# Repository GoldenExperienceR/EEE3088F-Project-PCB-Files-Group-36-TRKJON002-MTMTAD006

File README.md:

# EEE3088F-Project-PCB-Files-Group-36-TRKJON002-MTMTAD006

EEE3088F Project Power PCB KiCad Design

## Project Overview

This repository contains the design files for the power PCB subsystem of a micro mouse robot, a project undertaken as part of the EEE3088F course. The power PCB is a crucial component responsible for providing and managing power for the entire micro mouse system, enabling its autonomous navigation capabilities.

## Project Requirements

The power PCB design is required to meet the following specifications:

* Operate up to 4 motors bidirectionally. These include 2x brushed DC motors which could each draw 200mA at the highest voltage of a 1S1P battery. The other 2x motors are for the auxiliary connection and need to operate 500mA each.
* Place an INA219 for monitoring the battery on the I2C Bus and configure it correctly with respect to the hardware (cannot have BOTH A0 AND A1 on GND).
* Charge the battery from the 9V input pin.
* Have two charging modes for a higher and lower charging current for the battery (200mA ±100mA, and approximately 600mA±100mA from the battery perspective).
* Integrate USB C and get 9V out of the USB Host.
* Provide 2x External Load Switching at 1A each (High Side connected to your 5V).
* Provide a 3v3 5% accuracy (300mA max) and 5V Out 5% accuracy (1.5A max).
* Provide an ON/OFF switch. **OFF state:** battery draw <30uA. **ON state:** can provide your robot peak current of 2A. The switch needs to shut down 5V and 3V3.

## Repository Structure

This repository utilizes the following branches to manage the project's development:

* **main:** This branch contains the first iteration of the PCB design.
* **jonathans\_branch:** This branch includes separate modifications that were developed and subsequently merged into the `main` branch.
* **design2:** This branch represents the culmination of all changes made throughout the project and contains the final design of the power PCB. For the latest and final version of the design, please refer to this branch.

## Cloning Instructions
To obtain the latest version of the power PCB design, you can clone the `design2` branch directly using the following command:

```bash
git clone -b design2 [https://github.com/GoldenExperienceR/EEE3088F-Project-PCB-Files-Group-36-TRKJON002-MTMTAD006.git](https://github.com/GoldenExperienceR/EEE3088F-Project-PCB-Files-Group-36-TRKJON002-MTMTAD006.git)

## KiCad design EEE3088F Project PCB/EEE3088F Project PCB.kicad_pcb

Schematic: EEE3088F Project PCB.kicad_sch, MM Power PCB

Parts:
C1, C6: 0.01uF; C_0805_2012Metric_Pad1.18x1.45mm_HandSolder
C2, C4: 2.2uF; C_0603_1608Metric_Pad1.08x0.95mm_HandSolder
C3, C5, C21: 10uF; C_0805_2012Metric_Pad1.18x1.45mm_HandSolder
C7: 10uF; C_0402_1005Metric_Pad0.74x0.62mm_HandSolder
C8, C11, C12, C13, C14, C15, C17: 1uF; CAPC3216X180N
C16, C18: 0.1uF; C_0402_1005Metric_Pad0.74x0.62mm_HandSolder
C19: 0.33u; C_0805_2012Metric_Pad1.18x1.45mm_HandSolder
C20: 0.1u; C_0402_1005Metric_Pad0.74x0.62mm_HandSolder
D1: MBR230LS; D_SOD-123F
H1: MountingHole; MountingHole_2.2mm_M2_DIN965_Pad
J1: JST PH 2.00mm connector; JST_PH_S2B-PH-K_1x02_P2.00mm_Horizontal
J2: HRO_TYPE-C-31-M-12
JP1: V_BATT_CHRG Bridge; SolderJumper-2_P1.3mm_Bridged2Bar_Pad1.0x1.5mm
JP2: R_PROG_1 Bridge; SolderJumper-3_P1.3mm_Bridged2Bar12_RoundedPad1.0x1.5mm_Num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
JP3: R_PROG_2 Bridge; SolderJumper-3_P1.3mm_Bridged2Bar12_RoundedPad1.0x1.5mm_Num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
JP4, JP5, JP6, JP7, JP8, JP9, JP10: SolderJumper_2_Open; SolderJumper-2_P1.3mm_Open_RoundedPad1.0x1.5mm
JP11: SolderJumper_2_Bridged; SolderJumper-2_P1.3mm_Bridged2Bar_RoundedPad1.0x1.5mm
L1: 22uH; L_Coilcraft_1515SQ-47N
Q1: NPN; SOT-23_Handsoldering
R1, R2: 3.3k; R_0603_1608Metric
R3: 1k; RESC3115X65N
R4: 10k; RESC3115X65N
R5: 470; R_0805_2012Metric_Pad1.20x1.40mm_HandSolder
R6, R11, R12, R14: 160m; R_2512_6332Metric_Pad1.40x3.35mm_HandSolder
R7: 300; R_0805_2012Metric_Pad1.20x1.40mm_HandSolder
R8: 2200; R_0603_1608Metric_Pad0.98x0.95mm_HandSolder
R9, R10: 10; R_1206_3216Metric_Pad1.30x1.75mm_HandSolder
R13: 100; R_0805_2012Metric_Pad1.20x1.40mm_HandSolder
R_PROG_1: 2k; R_0402_1005Metric_Pad0.72x0.64mm_HandSolder
R_PROG_2: 6.2k; R_0603_1608Metric
S1: 74LVC2G66DP; Manufacturer_Part_Number 74LVC2G66DP; Mouser Part Number N/A
SW1: SS-12D10L3; SS-12D10G5_XKB
TP1: HV Test Point; TestPoint_Pad_1.0x1.0mm
TP3, TP7, TP9: TestPoint; TestPoint_Pad_2.0x2.0mm
TP4, TP6, TP8, TP10, TP11, TP12, TP13, TP18, TP19, TP20, TP21: TestPoint; TestPoint_Pad_1.0x1.0mm
U1: DRV8833PWR; TSSOP-16-1EP_4.4x5mm_P0.65mm_EP3x3mm
U2: DRV8833PWPR; TSSOP-16-1EP_4.4x5mm_P0.65mm_EP3x3mm
U3: INA219AxD; TSOT-23-8
U4: CH224K; SSOP-10-1EP_3.9x4.9mm_P1mm_EP2.1x3.3mm
U6: MIC5504-1.2YM5; SOT-23-5
U7: SX1308; SOT-23-6
U8, U9: TPS22965DSGR; DFN-8-1EP_2x2mm_P0.5mm_EP0.9x1.6mm; DigiKey_Part_Number 296-39362-2-ND
U10: LM7805L-TF3-T; TO-220F-3_Vertical
U11: TC4056A.; SOIC127P600X175-9N
am1: 2x16 (2.54mm pin pitch) pin header; PinHeader_2x16_P2.54mm_Vertical

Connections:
/2E: JP11.2 (B), R13.2, S1.3 (2E), TP6.1
/3V3 Out: C12.1, S1.8 (VCC), TP7.1, U6.5 (VOUT), am1.18
/5V Out: C13.1, C15.2, C17.2, D1.1 (K), R8.1, R13.1, TP9.1, U8.1 (VIN), U8.2 (VIN), U8.4 (VBIAS), U9.1 (VIN), U9.2 (VIN), U9.4 (VBIAS), am1.20
/Battery: J1.1, JP4.1 (A), JP7.2 (B), JP8.1 (A), R6.2, SW1.3, TP8.1, U3.2 (A0), am1.14
/CC1: J2.A5 (CC1), U4.7 (CC1)
/CC2: J2.B5 (CC2), U4.6 (CC2)
/CTRL_EXT_LOAD1: U8.3 (ON), am1.25
/CTRL_EXT_LOAD2: U9.3 (ON), am1.7
/DN: J2.A7 (DN), J2.B7 (DN), U4.5 (DM)
/DP: J2.A6 (DP), J2.B6 (DP), U4.4 (DP)
/EXT_LOAD1_OUT: C16.2, JP9.2 (B), R9.1, U8.7 (VOUT), U8.8 (VOUT), am1.21
/EXT_LOAD2_OUT: C18.2, JP10.2 (B), R10.1, U9.7 (VOUT), U9.8 (VOUT), am1.11
/FAST_CHARGE_CTRL: R5.1, S1.7 (1E), TP4.1, am1.13
/HV: C19.1, TP1.1, U4.10 (PG), U10.1 (VI), am1.22
/I2C1_SCL: R2.1, am1.16
/I2C1_SDA: R1.2, am1.17
/MOTOR1_A_OUT: U1.2 (AOUT1), am1.32
/MOTOR1_B_OUT: U1.4 (AOUT2), am1.31
/MOTOR1_CTRL1: TP10.1, U1.16 (AIN1), am1.28
/MOTOR1_CTRL2: TP11.1, U1.15 (AIN2), am1.30
/MOTOR2_CTRL1: TP12.1, U1.9 (BIN1), am1.4
/MOTOR2_CTRL2: TP13.1, U1.10 (BIN2), am1.6
/MOTOR3_A_OUT: JP5.1 (A), R12.2, am1.27
/MOTOR3_B_OUT: U2.4 (AOUT2), am1.29
/MOTOR3_CTRL1: TP18.1, U2.16 (AIN1), am1.24
/MOTOR3_CTRL2: TP19.1, U2.15 (AIN2), am1.26
/MOTOR4_CTRL1: TP20.1, U2.9 (BIN1), am1.8
/MOTOR4_CTRL2: TP21.1, U2.10 (BIN2), am1.10
/Motor2_A_OUT: U1.7 (BOUT1), am1.2
/Motor2_B_OUT: U1.5 (BOUT2), am1.1
/Motor4_A_OUT: JP6.1 (A), R14.1, am1.3
/Motor4_B_OUT: U2.5 (BOUT2), am1.5
/PROG: R_PROG_1.2, R_PROG_2.1, U11.2 (PROG)
/USART2_RX: am1.9
/USART2_TX: am1.12
/VBUS: J2.A4_B9 (VBUS), J2.B4_A9 (VBUS), R3.1, R4.1
/VDD: C8.1, R3.2, U4.1 (VDD)
/V_BATT_CHRG: C20.1, JP1.1 (A), U10.3 (VO)
/V_sensing: C1.1, C3.2, C5.2, C6.1, C11.1, C14.1, JP7.1 (A), L1.1, R11.1, U1.12 (VM), U2.12 (VM), U3.7 (IN-), U6.1 (VIN), U7.5 (IN)
/V_switch: C7.1, JP8.2 (B), R11.2, SW1.2, U3.5 (VS), U3.8 (IN+), U6.3 (EN), U7.4 (EN)
GND: C2.1, C3.1, C4.1, C5.1, C7.2, C8.2, C11.2, C12.2, C13.2, C14.2, C15.1, C16.1, C17.1, C18.1, C19.2, C20.2, C21.1, J1.2, J2.A1_B12 (GND), J2.B1_A12 (GND), J2.S1 (shield), JP2.3 (B), JP3.3 (B), JP9.1 (A), JP10.1 (A), Q1.3 (E), R7.2, R9.2, R10.2, S1.1 (1Y), S1.4 (GND), S1.5 (2Y), SW1.1, TP3.1, U1.3 (AISEN), U1.6 (BISEN), U1.13 (GND), U1.17 (GND), U2.3 (AISEN), U2.6 (BISEN), U2.13 (GND), U2.17 (GND), U3.1 (A1), U3.6 (GND), U4.2 (CFG2), U4.3 (CFG3), U4.9 (CFG1), U4.11 (GND), U6.2 (GND), U7.2 (GND), U8.5 (GND), U8.6 (CT), U8.9 (GND), U8.9_1 (GND), U8.9_2 (GND), U9.5 (GND), U9.6 (CT), U9.9 (GND), U9.9_1 (GND), U9.9_2 (GND), U10.2 (GND), U11.3 (GND), am1.19, am1.23; also elsewhere on the board
unnamed: D1.2 (A), L1.2, U7.1 (SW)
unnamed: JP1.2 (B), U11.4 (VCC)
unnamed: JP2.1 (A), R_PROG_1.1
unnamed: JP2.2 (C), S1.2 (1Z)
unnamed: JP3.1 (A), S1.6 (2Z)
unnamed: JP3.2 (C), R_PROG_2.2
unnamed: C21.2, JP4.2 (B), R6.1, U11.5 (BAT)
unnamed: JP5.2 (B), R12.1, U2.2 (AOUT1)
unnamed: JP6.2 (B), R14.2, U2.7 (BOUT1)
unnamed 50: JP11.1 (A), Q1.1 (C); also elsewhere on the board
unnamed 51: Q1.2 (B), R5.2; also elsewhere on the board
unnamed: C1.2, U1.11 (VCP)
unnamed: C2.2, U1.14 (VINT)
unnamed: C6.2, U2.11 (VCP)
unnamed: C4.2, U2.14 (VINT)
unnamed: R2.2, U3.4 (SCL)
unnamed: R1.1, U3.3 (SDA)
unnamed: R4.2, U4.8 (VBUS)
unnamed: R7.1, R8.2, U7.3 (FB)

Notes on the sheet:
PIN CONNECTORS AND BATTERY CONNECTOR
INA219 BATTERY CURRENT SENSOR
USB INTEGRATION
Fast and Slow Charging Modes
MOTOR DRIVER
x2 Load switching at 1 A
ON/OFF switch
3V3 300mA voltage regulator
5v 1.5A voltage regulator

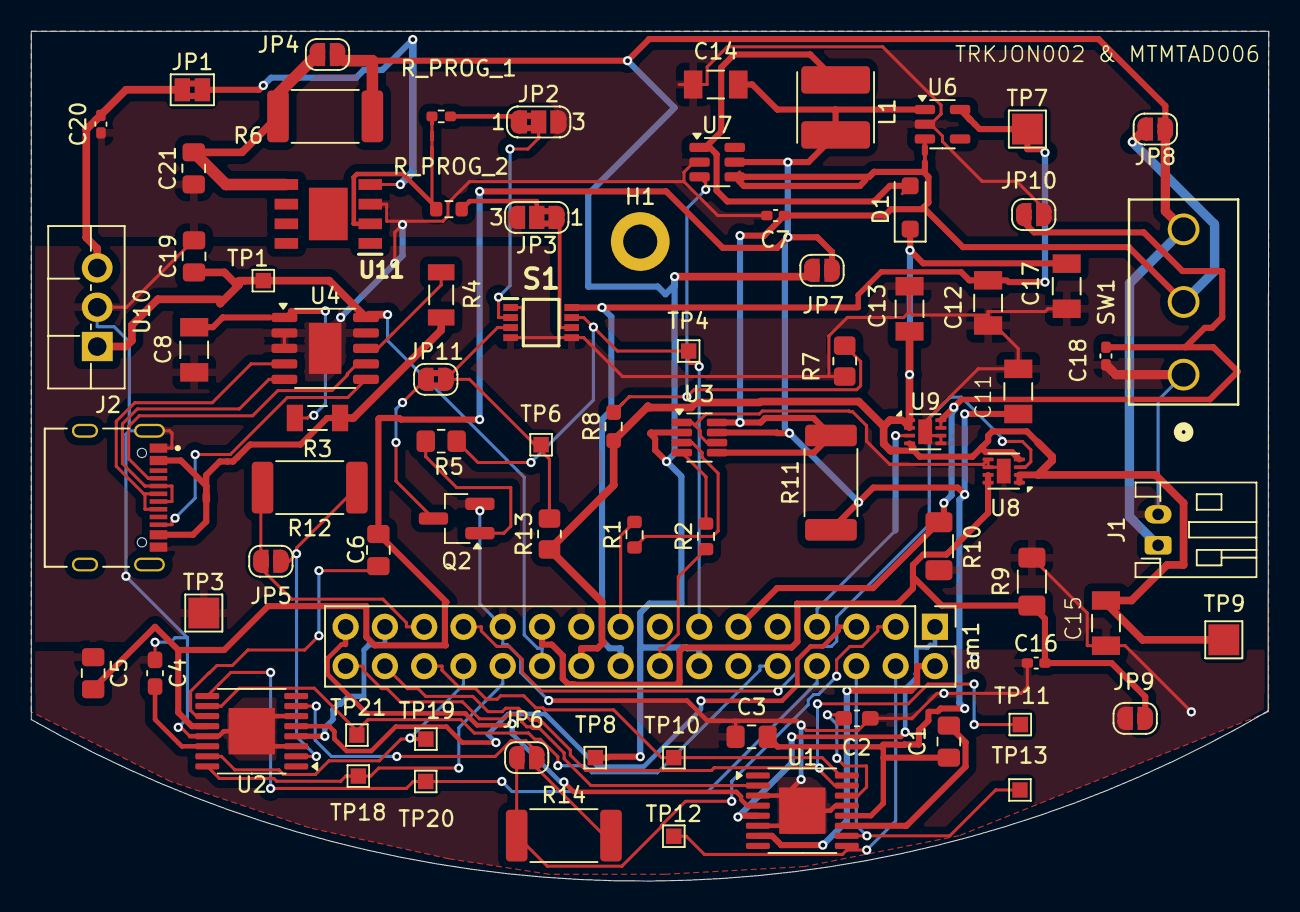
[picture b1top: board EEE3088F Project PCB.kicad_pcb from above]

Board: 2 copper layers, 80.0 x 54.9 mm, 80 parts (0 on the bottom side), 58 nets.

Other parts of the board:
Q2: NPN; SOT-23_Handsoldering

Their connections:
GND: Q2.2 (E); also elsewhere on the board
unnamed 50: Q2.3 (C); also elsewhere on the board
unnamed 51: Q2.1 (B); also elsewhere on the board

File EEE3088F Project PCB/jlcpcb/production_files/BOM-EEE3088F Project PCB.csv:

Comment,Designator,Footprint,LCSC,Quantity
TPS22965DSGR,"U8,U9",DFN-8-1EP_2x2mm_P0.5mm_EP0.9x1.6mm,C122837,2
0.1uF,"C16,C18,C20",C_0402_1005Metric_Pad0.74x0.62mm_HandSolder,C1525,3
10uF,C7,C_0402_1005Metric_Pad0.74x0.62mm_HandSolder,C15525,1
10uF,"C21,C3,C5",C_0805_2012Metric_Pad1.18x1.45mm_HandSolder,C15850,3
~,J2,HRO_TYPE-C-31-M-12,C165948,1
0.01uF,"C1,C6",C_0805_2012Metric_Pad1.18x1.45mm_HandSolder,C1710,2
300,R7,R_0805_2012Metric_Pad1.20x1.40mm_HandSolder,C17617,1
100,"R13,R5",R_0805_2012Metric_Pad1.20x1.40mm_HandSolder,C17710,2
10k,R4,RESC3115X65N,C17902,1
10,"R10,R9",R_1206_3216Metric_Pad1.30x1.75mm_HandSolder,C17903,2
1uF,"C11,C12,C13,C14,C15,C17,C8",CAPC3216X180N,C1848,7
NPN,Q2,SOT-23_Handsoldering,C2145,1
3.3k,"R1,R2",R_0603_1608Metric,C22978,2
2.2uF,"C2,C4",C_0603_1608Metric_Pad1.08x0.95mm_HandSolder,C23630,2
74LVC2G66DP,S1,74LVC2G66DP,C282354,1
22uH,L1,L_Coilcraft_1515SQ-47N,C2929420,1
SS-12D10L3,SW1,SS-12D10G5_XKB,C319013,1
0.33u,C19,C_0805_2012Metric_Pad1.18x1.45mm_HandSolder,C342635,1
MBR230LS,D1,D_SOD-123F,C391533,1
2k,R_PROG_1,R_0402_1005Metric_Pad0.72x0.64mm_HandSolder,C4109,1
2200,R8,R_0603_1608Metric_Pad0.98x0.95mm_HandSolder,C4190,1
6.2k,R_PROG_2,R_0603_1608Metric,C4260,1
1k,R3,RESC3115X65N,C4410,1
DRV8833PWR,"U1,U2",TSSOP-16-1EP_4.4x5mm_P0.65mm_EP3x3mm,C50506,2
160m,"R11,R12,R14,R6",R_2512_6332Metric_Pad1.40x3.35mm_HandSolder,C5375485,4
LM7805L-TF3-T,U10,TO-220F-3_Vertical,C71107,1
TC4056A.,U11,SOIC127P600X175-9N,C7588528,1
SX1308,U7,SOT-23-6,C78162,1
INA219AxD,U3,TSOT-23-8,C87469,1
MIC5504-1.2YM5,U6,SOT-23-5,C88419,1
CH224K,U4,SSOP-10-1EP_3.9x4.9mm_P1mm_EP2.1x3.3mm,C970725,1
JST PH 2.00mm connector,J1,JST_PH_S2B-PH-K_1x02_P2.00mm_Horizontal,,1
2x16 (2.54mm pin pitch) pin header,am1,PinHeader_2x16_P2.54mm_Vertical,,1
HV Test Point,TP1,TestPoint_Pad_1.0x1.0mm,,1
TestPoint,TP4,TestPoint_Pad_1.0x1.0mm,,1
TestPoint,TP6,TestPoint_Pad_1.0x1.0mm,,1
TestPoint,TP3,TestPoint_Pad_2.0x2.0mm,,1
TestPoint,TP7,TestPoint_Pad_2.0x2.0mm,,1
TestPoint,TP9,TestPoint_Pad_2.0x2.0mm,,1
TestPoint,TP19,TestPoint_Pad_1.0x1.0mm,,1
TestPoint,TP10,TestPoint_Pad_1.0x1.0mm,,1
TestPoint,TP21,TestPoint_Pad_1.0x1.0mm,,1
TestPoint,TP20,TestPoint_Pad_1.0x1.0mm,,1
TestPoint,TP18,TestPoint_Pad_1.0x1.0mm,,1
TestPoint,TP13,TestPoint_Pad_1.0x1.0mm,,1
TestPoint,TP12,TestPoint_Pad_1.0x1.0mm,,1
TestPoint,TP11,TestPoint_Pad_1.0x1.0mm,,1
TestPoint,TP8,TestPoint_Pad_1.0x1.0mm,,1

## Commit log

2025-03-21 intial commit
2025-03-22 added resistor in parallel
2025-03-22 commiting local changes 22/03/2025
2025-03-22 resistor in series with a LED
2025-03-22 resistor in parallel
2025-03-23 2x16 pin connector & JST PH 2.00 connector
2025-03-25 added pin net labels to connectors
2025-03-25 added a calaculations section, and my motor driver circuit
2025-03-25 adjusted layout slightly
2025-03-26 completed power module
2025-03-26 3/26/2025 - 8:00pm
2025-03-26 Resolved merge conflicts and merged jonathans_branch into main
2025-03-26 Added Current sensor INA219
2025-03-26 Added current sensor
2025-03-27 adjustments
2025-03-27 corrected sensor design and relabelled Vcc label to Battery
2025-03-27 added footprints to all motor driver components
2025-03-28 added usb c integration with footprints
2025-03-28 added regulatores, updated outputs, added on/off switch
2025-03-28 adjusted shunt resistance
2025-03-28 finished circuit
2025-04-01 Added student numbers, corrected board boundries, placed connectors (USB, JST, & pin headers)
2025-04-05 added fault managment and testing points for USB Integration and Charging requirments
2025-04-05 ajusted some testing points and added footprints for USB integration + half of the charging requirments
2025-04-07 added footprints to all my componets, placed all components on the board, and added all my jlcpcb part numbers
2025-04-08 confimed all tadala footprints, as well as placed all footprints on PCB board
2025-04-08 Adjusted arrangments on board, and assigned all JLCP part numbers
2025-04-08 adjusted footprints to match jlcpcb parts
2025-04-08 adjusted position of 2*16 connector
2025-04-08 updated the layout of the PCB to better make use of space
2025-04-09 changed inverter IC to a npn inverting switch, assigned new part numbers, added routing with no diameter considerations, added mounting holes,made component designators more visible, added copper fil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
2025-04-09 completed the first iteration where all routing is completed
2025-04-09 Added VBAT plane
2025-04-09 competed half my routing adjustments and removed DRC errors, noted a pproblem with the Q1 symbol
2025-04-09 finshed routing for Jonathan and half of Tadalas routing
2025-04-09 adjusted wiring width
2025-04-09 passed all DRC's
2025-05-14 Update README.md
    Added information about project requirements, the repos' structure and how clone the repo to obtain the latest PCB design.
